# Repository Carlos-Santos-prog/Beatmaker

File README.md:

# 🥁 Beatmaker — Pad Controller / Drum Machine / Groovebox

Groovebox autónomo con **16 pads sensibles a la velocidad**, secuenciador de pasos y **salida USB-MIDI**, construido sobre **Teensy 4.1** y la **Teensy Audio Library**.

El dispositivo genera y reproduce su propio audio, sin depender de un DAW ni de una computadora para sonar. Opcionalmente, al conectarlo por USB, funciona también como controlador MIDI para un DAW.

> **Estado:** en desarrollo · Plan de ejecución: 4 meses / 5 personas

---

## Características

- 16 pads en matriz 4×4 con sensores FSR (velocity continua; aftertouch posible a futuro)
- Reproductor de samples polifónico (8–16 voces) desde microSD
- Step-sequencer de 16 pasos con patrones encadenables
- USB-MIDI class-compliant, sin drivers
- Pantalla OLED (BPM, patrón activo, kit), encoders rotativos y LEDs RGB por pad
- Salida de audio estéreo vía DAC I2S PCM5102
- MIDI DIN opcional, sujeto a tiempo disponible

**Fuera de alcance en v1:** captura de audio en vivo (looper con micrófono/línea) y síntesis compleja en tiempo real (posible fase 2 sin cambios de hardware).

---

## Hardware

| Subsistema | Componente / Solución |
|---|---|
| Microcontrolador | Teensy 4.1 (NXP iMXRT1062, Cortex-M7 @ 600 MHz, 1 MB RAM, microSD nativo, 2× I2S/TDM, 1× S/PDIF) |
| Sensado de pads | 16 FSR + multiplexor analógico 74HC4067 |
| Acondicionamiento | Filtro RC paso-bajo (~1–2 kHz) por canal |
| Audio | DAC PCM5102 (I2S, sin configuración I2C) |
| Pantalla | OLED SSD1306 (I2C) |
| Feedback visual | LEDs RGB direccionables WS2812B / SK6812 |
| Navegación | Encoders rotativos (interrupción de cuadratura) |
| Almacenamiento | microSD (bancos de samples / kits) |

**Decisiones de diseño**

- **Crosstalk:** debounce en firmware que ignora picos a menos de 2–3 ms de un golpe en un pad adyacente.
- **Velocity:** valor leído en una ventana de ~3–5 ms tras cruzar el umbral, mapeado a 0–127 con una tabla de lookup no lineal y ajustable.
- **Ruido de audio:** tierras analógica y digital separadas (star ground cerca del códec) y LDO de bajo ruido dedicado a la sección analógica.
- **LEDs:** controlados por un periférico dedicado (DMA/timer) para no interferir con el bus I2S.

---

## Firmware

### Prioridades de tiempo real

Objetivo: latencia golpe → sonido **menor a 10 ms**.

1. **Máxima:** interrupción/DMA del códec de audio (nunca se bloquea)
2. **Alta:** escaneo de pads (timer periódico ~1 ms)
3. **Media:** generación y envío de mensajes MIDI
4. **Baja:** refresco de OLED y animación de LEDs (los primeros en saltarse un ciclo bajo carga)

### Motor de sonido y secuenciador

- Bloques de la Teensy Audio Library: mezclador, reproductor de SD, control de ganancia
- Kit activo cargado en RAM, con prefetch anticipado desde SD para evitar cortes
- Temporización del secuenciador referenciada al **contador de muestras de audio**, no a un timer de tiempo real, para evitar deriva entre patrones

### Referencia

[Dirtywave M8](https://github.com/Dirtywave) (`M8Firmware` / `M8HeadlessFirmware`): groovebox basado en Teensy, útil como plantilla para el pipeline de audio y el secuenciador.

---

## Uso como controlador MIDI

Conectado por USB, el beatmaker se reconoce como dispositivo MIDI class-compliant mediante `usbMIDI` de Teensyduino, sin librerías adicionales. Esto permite grabar tus golpes en Ableton Live o tocar instrumentos de Kontakt.

Guía de configuración paso a paso: [`docs/teensy-usbmidi-ableton-kontakt.pdf`](docs/teensy-usbmidi-ableton-kontakt.pdf)

---

## Plan de ejecución (16 semanas)

| Semanas | Fase | Entregable |
|---|---|---|
| 1–2 | Especificación congelada, pedido de componentes | Documento de especificación |
| 3–5 | Prototipo en protoboard (1–2 pads, audio desde SD, primer MIDI USB) | Subsistemas por separado |
| 6–7 | Integración de 16 pads + códec + primer secuenciador | Prototipo funcional en mesa |
| 8–9 | Diseño y envío de PCB v1, diseño de carcasa | Gerbers + modelo 3D |
| 10–11 | Bring-up de PCB v1 | PCB validada |
| 12–13 | Firmware final: UI, velocity calibrada, kits, pruebas de estrés | Firmware *feature-complete* |
| 14 | Ensamblaje en carcasa definitiva | Unidades terminadas |
| 15 | Pruebas con músicos externos | Reporte de pruebas |
| 16 | Pulido, documentación y demo | Producto + documentación |

> Una falla de PCB no corregible por software en las semanas 10–11 obligaría a una v2 (+2–3 semanas).

### Roles

1. **Hardware / PCB:** esquemático, componentes, PCB, fabricación, pruebas eléctricas
2. **Firmware Audio/DSP:** pipeline de audio, samples, mezclador, SD, latencia
3. **Firmware Control/MIDI:** pads, velocity, encoders, secuenciador, USB-MIDI, UI OLED
4. **Integración mecánica / CAD 3D:** carcasa, ergonomía, ensamblaje
5. **Pruebas / Software host / Documentación:** plan de pruebas, herramienta para cargar kits, docs, cronograma

### Riesgos principales

| Riesgo | Mitigación |
|---|---|
| Crosstalk / velocity poco fiable | Validar el acondicionamiento con un solo pad en protoboard desde la semana 3 |
| Ruido digital en el audio | Definir tierras y alimentación analógica dedicada desde el primer esquemático |
| Bring-up hardware-firmware subestimado | Reservar semanas 10–11 solo para esto, sin features nuevas |

---

## Estructura del repositorio

```
.
├── firmware/        # Código Teensy (Arduino/PlatformIO)
├── hardware/        # Esquemáticos, PCB, Gerbers, BOM
├── cad/             # Modelos 3D de la carcasa
├── docs/            # Informe técnico y documentación de referencia
│   ├── informe_beatmaker.pdf
│   ├── teensy-usbmidi-ableton-kontakt.pdf
│   └── teensy41-datasheet.pdf   (clave.pdf)
├── samples/         # Kits de ejemplo para la microSD
└── README.md
```

---

## Referencias

- [Teensy 4.1 (PJRC)](https://www.pjrc.com/store/teensy41.html)
- [Teensy USB-MIDI](https://www.pjrc.com/teensy/td_midi.html)
- [Teensyduino](https://www.pjrc.com/teensy/teensyduino.html)
- [Teensy Audio Library](https://www.pjrc.com/teensy/td_libs_Audio.html)
- [Dirtywave M8 Firmware](https://github.com/Dirtywave)

---

## Licencia

Por definir (por ejemplo, MIT para firmware y CERN-OHL para hardware).

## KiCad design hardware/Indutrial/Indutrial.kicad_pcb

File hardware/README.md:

# 🔌 Hardware

Diseño electrónico del beatmaker en **KiCad**: esquemáticos, PCB y archivos de fabricación.

## Contenido

```
hardware/
├── beatmaker.kicad_pro        # Proyecto de KiCad
├── *.kicad_sch                # Esquemáticos jerárquicos
├── *.kicad_pcb                # Diseño de la PCB
├── lib/                       # Símbolos y huellas propias
├── gerbers/                   # Exportación para fabricación
└── bom/                       # Lista de materiales
```

### Proyecto `Indutrial`

Estado actual del diseño, con la hoja raíz y las hojas de subsistemas:

```
hardware/Indutrial/
├── Indutrial.kicad_pro        # Proyecto de KiCad
├── Indutrial.kicad_sch        # Hoja raíz (interconexión entre hojas)
├── Indutrial.kicad_pcb        # Diseño de la PCB
├── DAC.kicad_sch              # Códec de audio (PCM5102)
├── regulador.kicad_sch        # Alimentación y regulación
├── QLED.kicad_sch             # Controles, OLED y LEDs RGB
└── untitled.kicad_sch         # Hoja de trabajo en curso
```

> Los archivos temporales/locales de KiCad (`.kicad_prl`, `~*.lck`, `#auto_saved_files#`, `*-backups/`, `_autosave-*`) están excluidos mediante `.gitignore`.

## Esquemáticos jerárquicos

El diseño se divide en hojas por subsistema:

| Hoja | Descripción |
|---|---|
| **Raíz** | Interconexión general entre hojas |
| **Matriz de pads** | 16 FSR, filtro RC por canal (~1–2 kHz) y multiplexor 74HC4067 |
| **Códec de audio** | DAC PCM5102 (I2S) con aislamiento de ruido |
| **Alimentación** | Regulación, y LDO de bajo ruido dedicado a la sección analógica |
| **Controles y UI** | Encoders, OLED SSD1306 (I2C) y LEDs RGB WS2812B |
| **MCU** | Teensy 4.1, microSD y conexión USB |

## Aislamiento del códec

Para evitar ruido digital en el audio ("whining", clics):

- Planos de tierra analógica y digital separados, unidos en un único punto (**star ground**) cerca del códec.
- LDO de bajo ruido dedicado para la sección analógica, distinto del riel digital de 3.3 V.
- Definir esta separación desde el primer esquemático, no como corrección posterior.

## Fabricación

La carpeta `gerbers/` contiene la exportación lista para enviar a fábrica:

- Archivos Gerber de todas las capas
- Archivo de taladrado (Excellon)
- BOM y archivo de posiciones (si se pide ensamblaje)

> **Importante:** regenera siempre los Gerbers desde KiCad tras cualquier cambio en la PCB para que no queden desactualizados.

## Reglas de diseño

- Validar el circuito de acondicionamiento FSR con **un solo pad en protoboard** antes de integrar los 16.
- Revisar con ERC y DRC antes de cada exportación.
- El cronograma asume **una sola iteración de PCB**; un error no corregible por software en bring-up implica una v2 (+2–3 semanas).

## Requisitos

- [KiCad](https://www.kicad.org/) (usa la misma versión mayor en todo el equipo para evitar incompatibilidades).

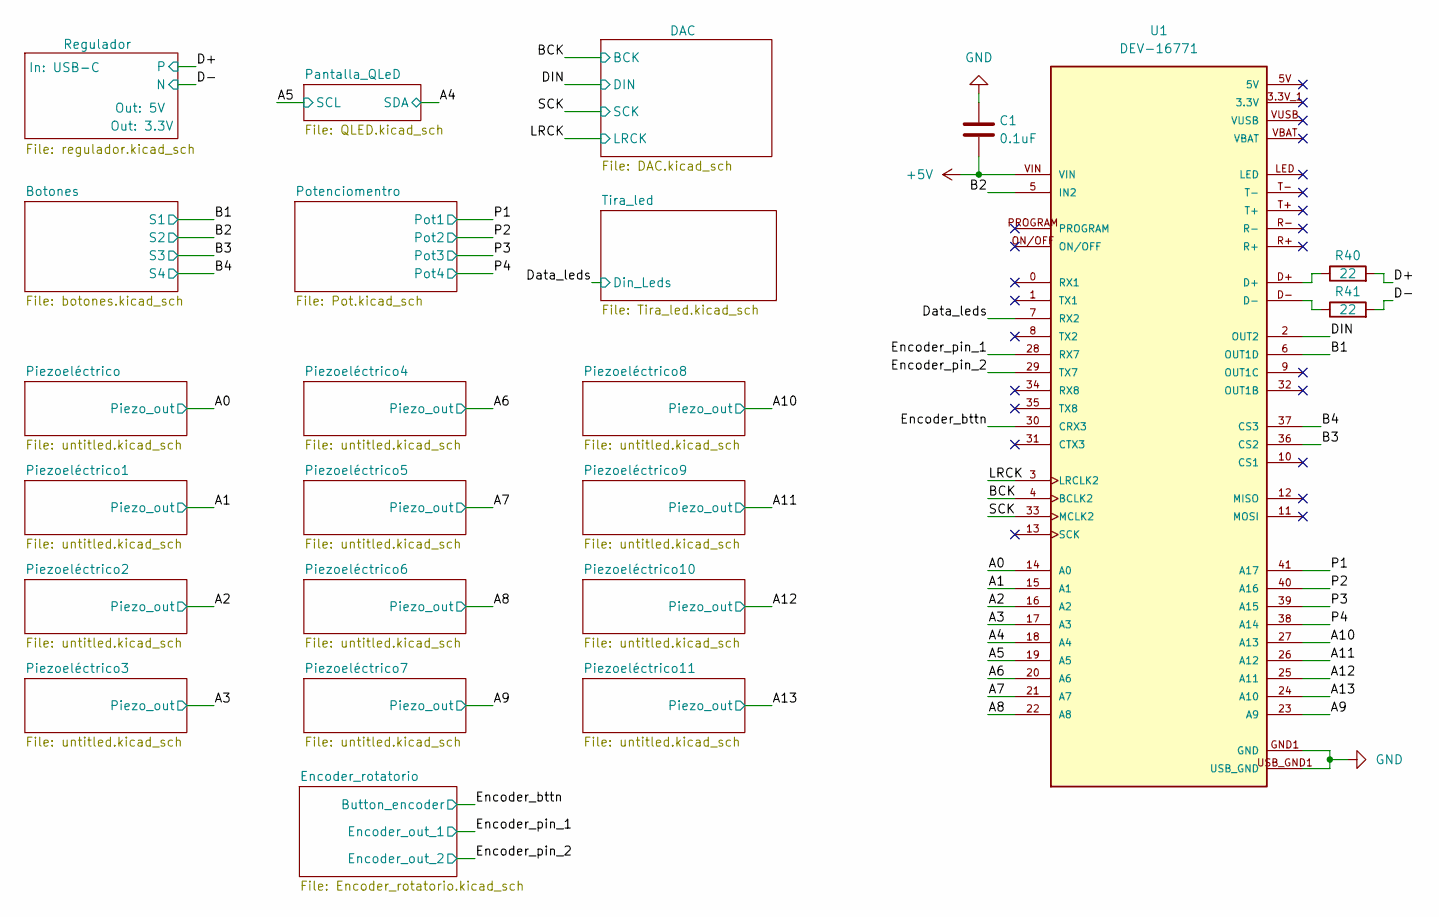
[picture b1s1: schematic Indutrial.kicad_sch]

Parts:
C1: 0.1uF; C_0603_1608Metric
R40, R41: 22; R_0603_1608Metric
U1: DEV-16771; MODULE_DEV-16771; MPN DEV-16771

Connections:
+5V: C1.2, U1.VIN; also elsewhere on the board
/A0: U1.14 (A0); also elsewhere on the board
/A1: U1.15 (A1); also elsewhere on the board
/A2: U1.16 (A2); also elsewhere on the board
/A3: U1.17 (A3); also elsewhere on the board
/A4: U1.18 (A4); also elsewhere on the board
/A5: U1.19 (A5); also elsewhere on the board
/A6: U1.20 (A6); also elsewhere on the board
/A7: U1.21 (A7); also elsewhere on the board
/A8: U1.22 (A8); also elsewhere on the board
/A9: U1.23 (A9); also elsewhere on the board
/A10: U1.27 (A13); also elsewhere on the board
/A11: U1.26 (A12); also elsewhere on the board
/A12: U1.25 (A11); also elsewhere on the board
/A13: U1.24 (A10); also elsewhere on the board
/B1: U1.6 (OUT1D); also elsewhere on the board
/B2: U1.5 (IN2); also elsewhere on the board
/B3: U1.36 (CS2); also elsewhere on the board
/B4: U1.37 (CS3); also elsewhere on the board
/BCK: U1.4 (BCLK2); also elsewhere on the board
/D+: R40.2; also elsewhere on the board
/D-: R41.2; also elsewhere on the board
/DIN: U1.2 (OUT2); also elsewhere on the board
/Data_leds: U1.7 (RX2); also elsewhere on the board
/Encoder_bttn: U1.30 (CRX3); also elsewhere on the board
/Encoder_pin_1: U1.28 (RX7); also elsewhere on the board
/Encoder_pin_2: U1.29 (TX7); also elsewhere on the board
/LRCK: U1.3 (LRCLK2); also elsewhere on the board
/P1: U1.41 (A17); also elsewhere on the board
/P2: U1.40 (A16); also elsewhere on the board
/P3: U1.39 (A15); also elsewhere on the board
/P4: U1.38 (A14); also elsewhere on the board
/SCK: U1.33 (MCLK2); also elsewhere on the board
GND: C1.1, U1.GND1 (GND), U1.GND2 (GND), U1.GND3 (GND), U1.GND4 (GND), U1.GND5 (GND), U1.USB_GND1 (USB_GND), U1.USB_GND2 (USB_GND); also elsewhere on the board
unnamed: R40.1, U1.D+
unnamed: R41.1, U1.D-

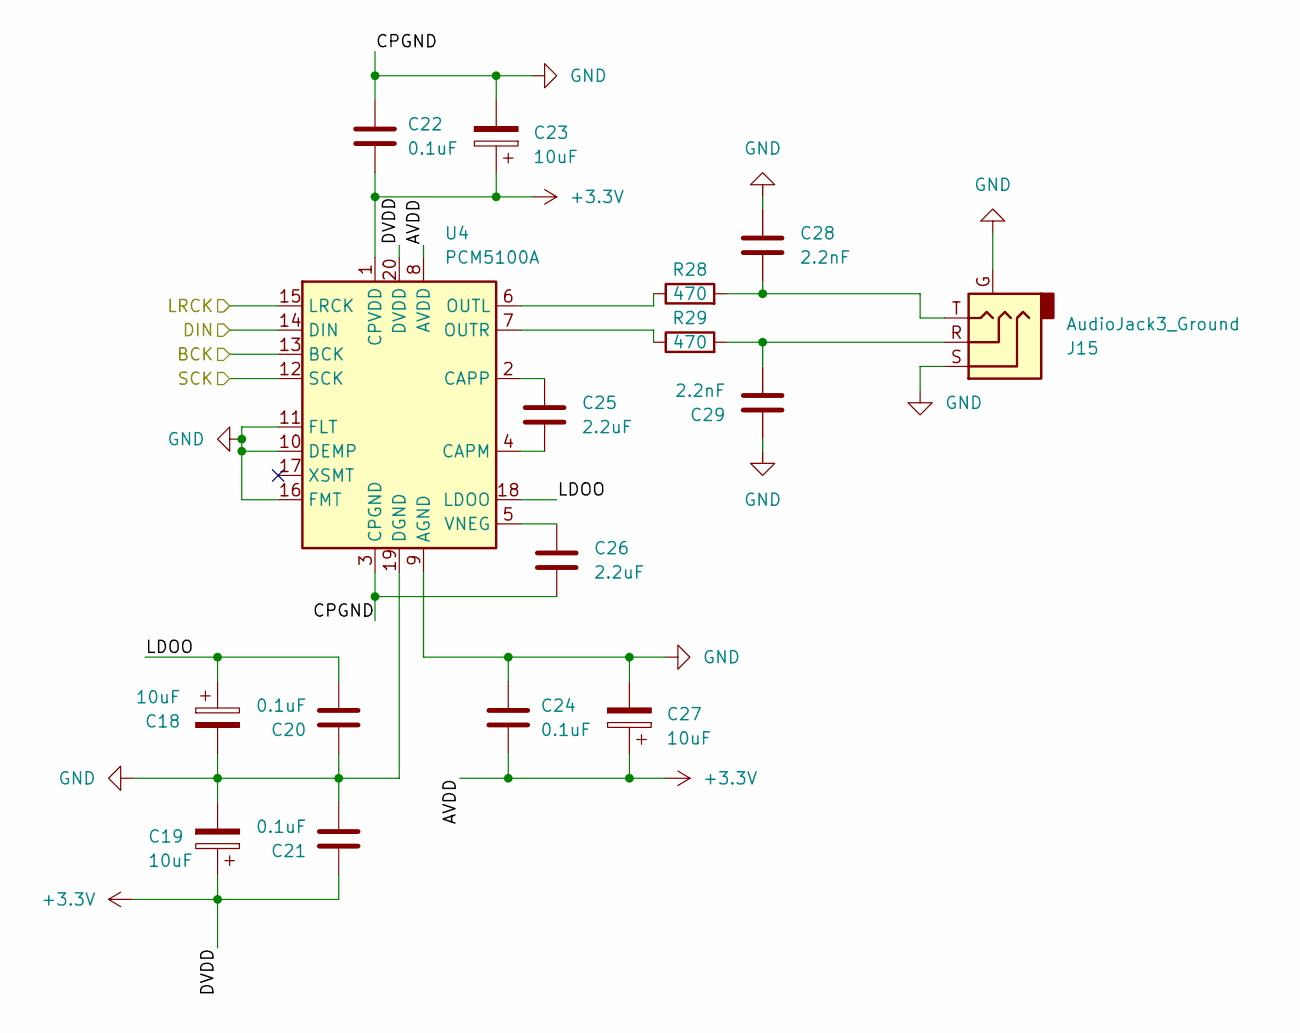
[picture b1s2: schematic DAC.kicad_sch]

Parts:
C18, C19: 10uF; C_1206_3216Metric
C20, C21, C22, C24: 0.1uF; C_0603_1608Metric
C23, C27: 10uF; CP_EIA-3216-18_Kemet-A
C25, C26: 2.2uF; C_0805_2012Metric
C28, C29: 2.2nF; C_0805_2012Metric_Pad1.18x1.45mm_HandSolder
J15: AudioJack3_Ground; Jack_3.5mm_CUI_SJ1-3524N_Horizontal
R28, R29: 470; R_1206_3216Metric
U4: PCM5100A; TSSOP-20_4.4x6.5mm_P0.65mm

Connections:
+3.3V: C19.1, C21.2, C22.1, C23.1, C24.1, C27.1, U4.1 (CPVDD), U4.8 (AVDD), U4.20 (DVDD); also elsewhere on the board
/BCK: U4.13 (BCK); also elsewhere on the board
/DAC/LDOO: C18.1, C20.1, U4.18 (LDOO)
/DIN: U4.14 (DIN); also elsewhere on the board
/LRCK: U4.15 (LRCK); also elsewhere on the board
/SCK: U4.12 (SCK); also elsewhere on the board
GND: C18.2, C19.2, C20.2, C21.1, C22.2, C23.2, C24.2, C26.1, C27.2, C28.1, C29.1, J15.G, J15.S, U4.3 (CPGND), U4.9 (AGND), U4.10 (DEMP), U4.11 (FLT), U4.16 (FMT), U4.19 (DGND); also elsewhere on the board
unnamed: C28.2, J15.T, R28.2
unnamed: C29.2, J15.R, R29.2
unnamed: C25.1, U4.4 (CAPM)
unnamed: C25.2, U4.2 (CAPP)
unnamed: R28.1, U4.6 (OUTL)
unnamed: R29.1, U4.7 (OUTR)
unnamed: C26.2, U4.5 (VNEG)

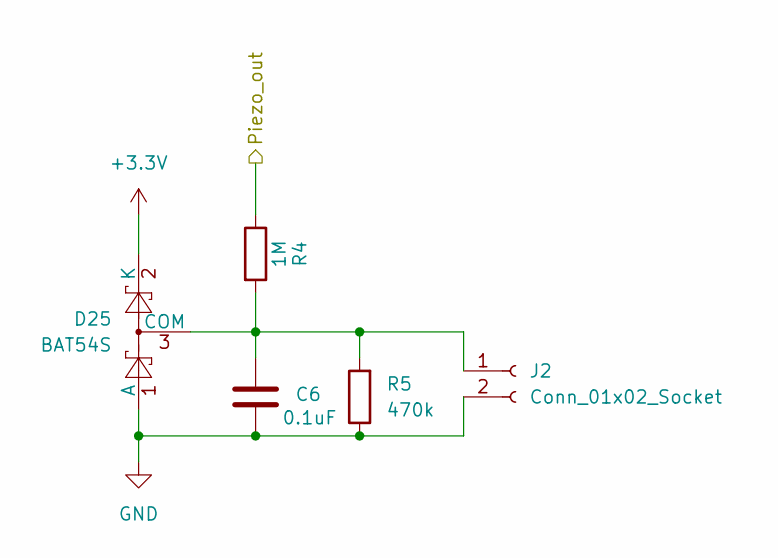
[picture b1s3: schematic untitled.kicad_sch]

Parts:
C6: 0.1uF; C_0603_1608Metric
D25: BAT54S; SOT-23
J2: Conn_01x02_Socket; SolderWire-0.1sqmm_1x02_P3.6mm_D0.4mm_OD1mm
R4: 1M; R_0603_1608Metric
R5: 470k; R_0603_1608Metric

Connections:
+3.3V: D25.2 (K); also elsewhere on the board
/A0: R4.1; also elsewhere on the board
GND: C6.2, D25.1 (A), J2.2, R5.1; also elsewhere on the board
unnamed: C6.1, D25.3 (COM), J2.1, R4.2, R5.2

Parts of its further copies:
C7, C8, C9, C10, C11, C12, C13, C14, C15, C16, C17: 0.1uF; C_0603_1608Metric
D26, D27, D28, D29, D30, D31, D32, D33, D34, D35, D36: BAT54S; SOT-23
J3, J4, J5, J6, J7, J8, J9, J10, J11, J12, J13: Conn_01x02_Socket; SolderWire-0.1sqmm_1x02_P3.6mm_D0.4mm_OD1mm
R6, R8, R10, R12, R14, R16, R18, R20, R22, R24, R26: 1M; R_0603_1608Metric
R7, R9, R11, R13, R15, R17, R19, R21, R23, R25, R27: 470k; R_0603_1608Metric

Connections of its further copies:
+3.3V: D26.2 (K), D27.2 (K), D28.2 (K), D29.2 (K), D30.2 (K), D31.2 (K), D32.2 (K), D33.2 (K), D34.2 (K), D35.2 (K), D36.2 (K); also elsewhere on the board
/A1: R6.1; also elsewhere on the board
/A2: R8.1; also elsewhere on the board
/A3: R10.1; also elsewhere on the board
/A6: R12.1; also elsewhere on the board
/A7: R14.1; also elsewhere on the board
/A8: R16.1; also elsewhere on the board
/A9: R18.1; also elsewhere on the board
/A10: R20.1; also elsewhere on the board
/A11: R22.1; also elsewhere on the board
/A12: R24.1; also elsewhere on the board
/A13: R26.1; also elsewhere on the board
GND: C7.2, C8.2, C9.2, C10.2, C11.2, C12.2, C13.2, C14.2, C15.2, C16.2, C17.2, D26.1 (A), D27.1 (A), D28.1 (A), D29.1 (A), D30.1 (A), D31.1 (A), D32.1 (A), D33.1 (A), D34.1 (A), D35.1 (A), D36.1 (A), J3.2, J4.2, J5.2, J6.2, J7.2, J8.2, J9.2, J10.2, J11.2, J12.2, J13.2, R7.1, R9.1, R11.1, R13.1, R15.1, R17.1, R19.1, R21.1, R23.1, R25.1, R27.1; also elsewhere on the board
unnamed: C7.1, D26.3 (COM), J3.1, R6.2, R7.2
unnamed: C8.1, D27.3 (COM), J4.1, R8.2, R9.2
unnamed: C9.1, D28.3 (COM), J5.1, R10.2, R11.2
unnamed: C10.1, D29.3 (COM), J6.1, R12.2, R13.2
unnamed: C11.1, D30.3 (COM), J7.1, R14.2, R15.2
unnamed: C12.1, D31.3 (COM), J8.1, R16.2, R17.2
unnamed: C13.1, D32.3 (COM), J9.1, R18.2, R19.2
unnamed: C14.1, D33.3 (COM), J10.1, R20.2, R21.2
unnamed: C15.1, D34.3 (COM), J11.1, R22.2, R23.2
unnamed: C16.1, D35.3 (COM), J12.1, R24.2, R25.2
unnamed: C17.1, D36.3 (COM), J13.1, R26.2, R27.2

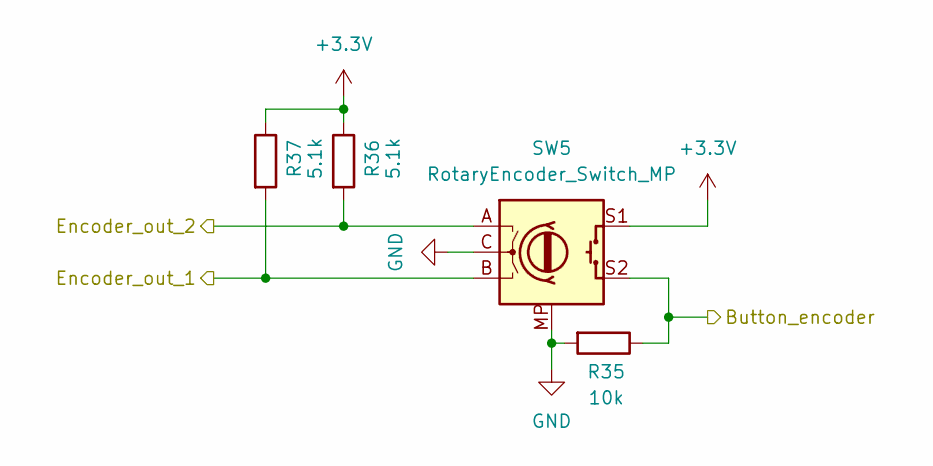
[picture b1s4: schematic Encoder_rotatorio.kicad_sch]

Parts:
R35: 10k; R_0603_1608Metric
R36, R37: 5.1k; R_0603_1608Metric
SW5: RotaryEncoder_Switch_MP; RotaryEncoder_Alps_EC11E-Switch_Vertical_H20mm

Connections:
+3.3V: R36.1, R37.1, SW5.S1; also elsewhere on the board
/Encoder_bttn: R35.1, SW5.S2; also elsewhere on the board
/Encoder_pin_1: R37.2, SW5.B; also elsewhere on the board
/Encoder_pin_2: R36.2, SW5.A; also elsewhere on the board
GND: R35.2, SW5.C, SW5.MP; also elsewhere on the board

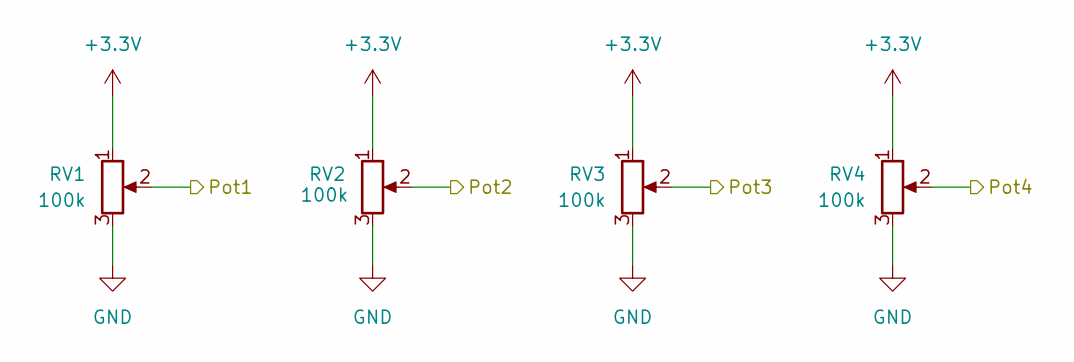
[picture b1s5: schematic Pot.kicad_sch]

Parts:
RV1, RV2, RV3, RV4: 100k; Potentiometer_Alpha_RD901F-40-00D_Single_Vertical

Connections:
+3.3V: RV1.1, RV2.1, RV3.1, RV4.1; also elsewhere on the board
/P1: RV1.2; also elsewhere on the board
/P2: RV2.2; also elsewhere on the board
/P3: RV3.2; also elsewhere on the board
/P4: RV4.2; also elsewhere on the board
GND: RV1.3, RV2.3, RV3.3, RV4.3; also elsewhere on the board

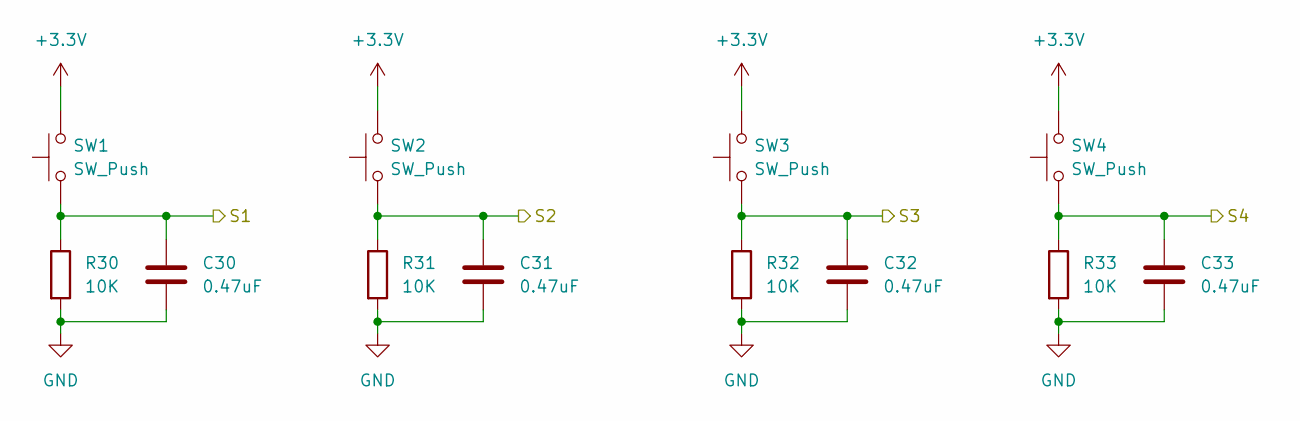
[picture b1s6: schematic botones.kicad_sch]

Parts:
C30, C31, C32, C33: 0.47uF; C_0805_2012Metric
R30, R31, R32, R33: 10K; R_0805_2012Metric
SW1, SW2, SW3, SW4: SW_Push; SW_PUSH_6mm

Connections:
+3.3V: SW1.2, SW2.2, SW3.2, SW4.2; also elsewhere on the board
/B1: C30.1, R30.1, SW1.1; also elsewhere on the board
/B2: C31.1, R31.1, SW2.1; also elsewhere on the board
/B3: C32.1, R32.1, SW3.1; also elsewhere on the board
/B4: C33.1, R33.1, SW4.1; also elsewhere on the board
GND: C30.2, C31.2, C32.2, C33.2, R30.2, R31.2, R32.2, R33.2; also elsewhere on the board

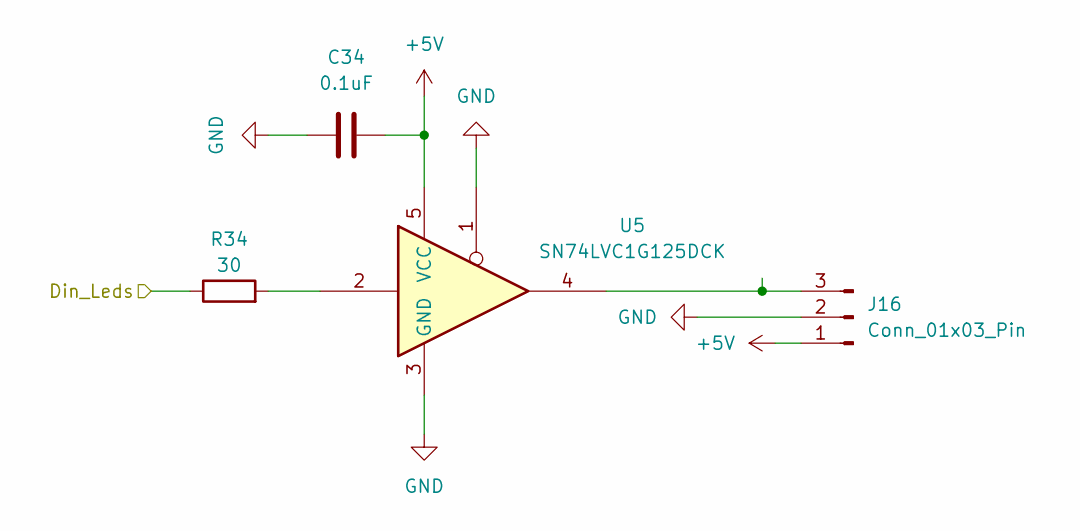
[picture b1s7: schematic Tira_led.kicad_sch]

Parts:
C34: 0.1uF; C_0805_2012Metric
J16: Conn_01x03_Pin; JST_EH_B3B-EH-A_1x03_P2.50mm_Vertical
R34: 30; R_1206_3216Metric
U5: SN74LVC1G125DCK; Texas_R-PDSO-G5_DCK-5

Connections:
+5V: C34.1, J16.1, U5.5 (VCC); also elsewhere on the board
/Data_leds: R34.1; also elsewhere on the board
GND: C34.2, J16.2, U5.1, U5.3 (GND); also elsewhere on the board
unnamed: J16.3, U5.4
unnamed: R34.2, U5.2

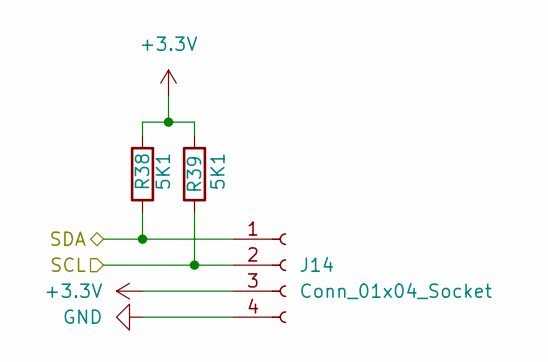
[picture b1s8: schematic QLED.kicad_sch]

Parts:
J14: Conn_01x04_Socket; PinSocket_1x04_P2.54mm_Vertical
R38, R39: 5K1; R_0805_2012Metric

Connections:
+3.3V: J14.3, R38.2, R39.2; also elsewhere on the board
/A4: J14.1, R38.1; also elsewhere on the board
/A5: J14.2, R39.1; also elsewhere on the board
GND: J14.4; also elsewhere on the board

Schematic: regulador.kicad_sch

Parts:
C3, C4: 47uF; CP_Elec_5x5.4
C5: 22uF; CP_Elec_4x4.5
C35, C38: 0.1uF; C_0805_2012Metric
C36: 1uF; CP_EIA-3216-18_Kemet-A
D1: SM6T10A; D_SMB_Handsoldering
J17: USB_C_Receptacle_USB2.0_16P; USB_C_Receptacle_G-Switch_GT-USB-7010ASV
R1, R2: 5K1; R_0805_2012Metric
R3: 50; R_0805_2012Metric
TP1, TP2, TP3: TestPoint; TestPoint_Pad_D1.5mm
U2: STEF05SGR; TSOT23-8L_STM
U3: AMS1117-3.3; SOT-223-3_TabPin2

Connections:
+3.3V: C5.1, TP3.1 (1_1), U3.2 (VO); also elsewhere on the board
+5V: C3.1, C4.1, C38.1, R3.1, TP2.1 (1_1), U2.5 (SOURCE/VOUT), U2.6 (SOURCE/VOUT), U3.3 (VI); also elsewhere on the board
/D+: J17.A6 (D+), J17.B6 (D+); also elsewhere on the board
/D-: J17.A7 (D-), J17.B7 (D-); also elsewhere on the board
GND: C3.2, C4.2, C5.2, C35.2, C36.2, C38.2, D1.2 (A2), J17.A1 (GND), J17.A12 (GND), J17.B1 (GND), J17.B12 (GND), J17.SH (SHIELD), R1.2, R2.2, U2.4 (GND), U3.1 (GND); also elsewhere on the board
unnamed: C35.1, C36.1, D1.1 (A1), J17.A4 (VBUS), J17.A9 (VBUS), J17.B4 (VBUS), J17.B9 (VBUS), TP1.1 (1_1), U2.7 (VCC), U2.8 (VCC)
unnamed: J17.A5 (CC1), R1.1
unnamed: J17.B5 (CC2), R2.1
unnamed: R3.2, U2.1 (ILIM)

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
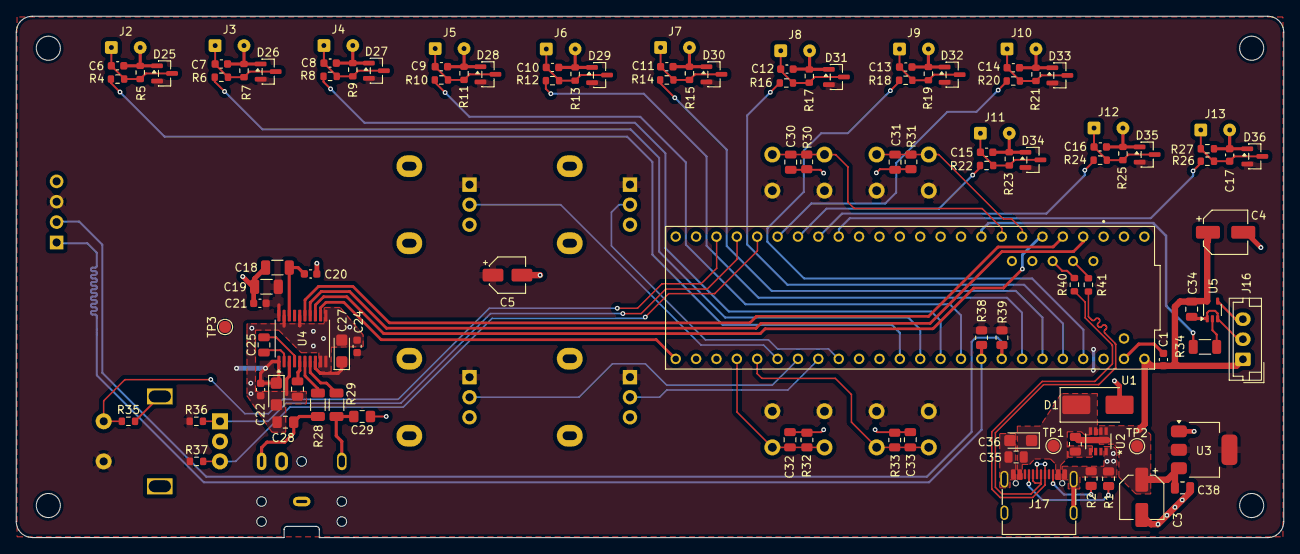
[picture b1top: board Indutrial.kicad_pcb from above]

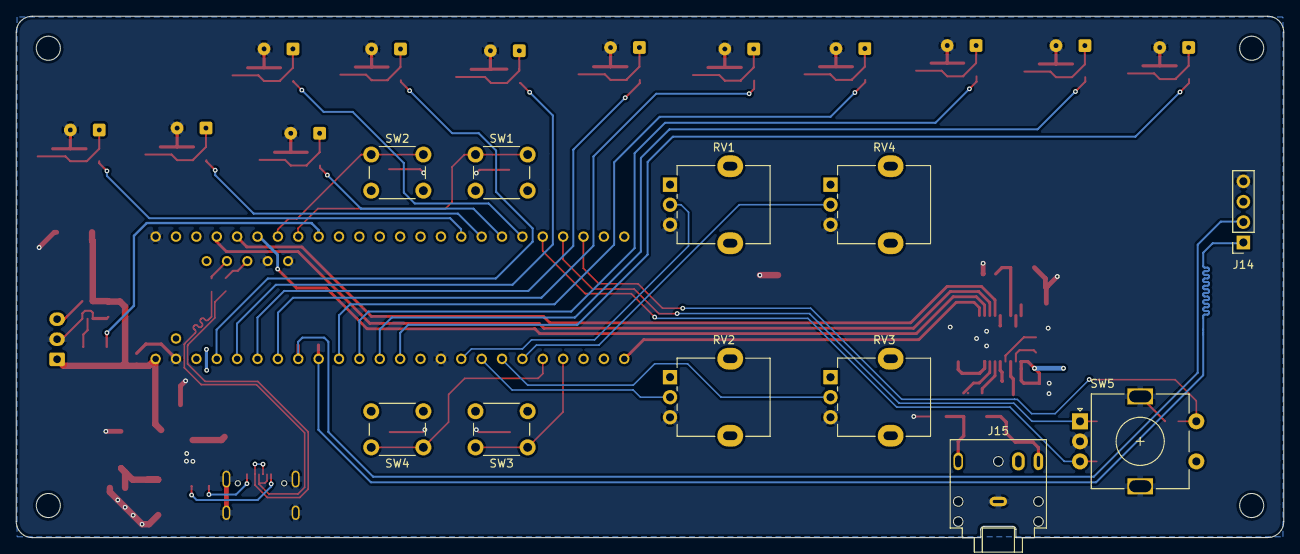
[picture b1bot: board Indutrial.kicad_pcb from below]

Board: 2 copper layers, 158.0 x 65.0 mm, 123 parts (11 on the bottom side), 63 nets.

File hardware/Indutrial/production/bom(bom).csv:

Comment;Designator;Footprint;JLCPCB Part #
50;R3;0805;C2828866
2.2uF;C25,C26;0805;C377773
470;R28,R29;1206;C114945
SN74LVC1G125DCK;U5;Texas_R-PDSO-G5_DCK-5;C55509833
BAT54S;D25,D26,D27,D28,D29,D30,D31,D32,D33,D34,D35,D36;SOT-23;C7420333
0.1uF;C1,C10,C11,C12,C13,C14,C15,C16,C17,C20,C21,C22,C24,C6,C7,C8,C9;0603;C14663
10uF;C23,C27;CP_EIA-3216-18_Kemet-A;C7171
22uF;C5;CP_Elec_4x4.5;C72502
10uF;C18,C19;1206;C13585
30;R34;1206;C137313
10K;R30,R31,R32,R33;0805;C17414
STEF05SGR;U2;TSOT23-8L_STM;C5271105
1uF;C36;CP_EIA-3216-18_Kemet-A;C7176
5K1;R1,R2,R38,R39;0805;C27834
PCM5100A;U4;TSSOP-20_4.4x6.5mm_P0.65mm;C131154
2.2nF;C28,C29;0805;C28260
22;R40,R41;0603;C23345
5.1k;R36,R37;0603;C23186
0.1uF;C34,C35,C38;0805;C49678
0.47uF;C30,C31,C32,C33;0805;C13967
1M;R10,R12,R14,R16,R18,R20,R22,R24,R26,R4,R6,R8;0603;C22935
SM6T10A;D1;D_SMB_Handsoldering;C133699
10k;R35;0603;C25804
AMS1117-3.3;U3;SOT-223-3_TabPin2;C6186
470k;R11,R13,R15,R17,R19,R21,R23,R25,R27,R5,R7,R9;0603;C23178
47uF;C3,C4;CP_Elec_5x5.4;C7469972
